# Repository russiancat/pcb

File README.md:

# PCB Auto-Router

A Python proof-of-concept for AI-assisted PCB routing. Import a KiCad board file, get it auto-routed in seconds.

**Status:** Active research / proof-of-concept. Not yet production-ready.

---

## What It Does

- Reads `.kicad_pcb` files (KiCad 7, 8, and 10 format)
- Auto-routes all nets using A* pathfinding on a 2-layer grid
- Supports copper pour (GND flood fill) on any layer
- Visualises the result as a two-panel image (top copper / bottom copper)
- Benchmarks against the existing routing in a file — measures completion %, wire length efficiency, via count, and DRC violations
- DRC checks: open nets, edge clearance, short circuits, pad clearance
- Manufacturer profiles with `merge()` for strictest-wins constraint checking

What it does **not** do (yet): schematic capture, auto-placement, Gerber export.

---

## Quick Start

```bash
# Install dependencies
python -m venv .venv
source .venv/bin/activate
pip install numpy matplotlib

# Route a KiCad board (outputs demo_result.png)
python kicad_demo.py path/to/your_board.kicad_pcb

# Run the benchmark across all demo boards
python benchmark.py
```

---

## Example Output

Two-panel view — top copper (F.Cu) and bottom copper (B.Cu) side by side.  
Legend below the board. GND copper pour shown as semi-transparent fill.

---

## Manufacturer Profiles

Profiles live in `router/profiles/*.toml`. Add a new manufacturer by adding one `.toml` file — no Python code needed.

| Profile | Trace / Clearance | Via drill | Via cost | Target |
|---------|------------------|-----------|----------|--------|
| `HOME_ETCH` | 1.0 mm | 0.8 mm | High | Toner transfer / UV home etching |
| `PCBWAY_2L` | 0.127 mm | 0.3 mm | Low | PCBWay 2-layer standard |
| `PCBWAY_4L` | 0.1 mm | 0.2 mm | Low | PCBWay 4-layer advanced |
| `JLCPCB_2L` | 0.127 mm | 0.3 mm | Low | JLCPCB 2-layer standard |
| `JLCPCB_4L` | 0.1 mm | 0.2 mm | Low | JLCPCB 4-layer advanced |
| `ZBOTIC_2L` | 0.15 mm | 0.3 mm | Low | ZBOTIC 2-layer |
| `ZBOTIC_4L` | 0.1 mm | 0.2 mm | Low | ZBOTIC 4-layer |

Change `PROFILE` at the top of `kicad_demo.py` to target a different fab.  
Use `ManufacturerProfile.merge(a, b)` to combine constraints (strictest-wins).

---

## Benchmark Results

Tested against KiCad demo boards using the same component placements, routing from scratch with a 0.5 mm benchmark grid (speed-optimised — use a manufacturer profile for real DRC).

| Board | Nets | Our routed | Our unrouted | KiCad routed | KiCad unrouted | Wire vs KiCad | Shorts | Quality |
|-------|------|-----------|-------------|-------------|---------------|---------------|--------|---------|
| multichannel_mixer | 80 | 79 (98.8%) | 1 | 79 (98.8%) | 1 | −7.0% shorter | ✓ | 75.9 |
| complex_hierarchy | 52 | 50 (96.2%) | 2 | 49 (94.2%) | 3 | −22.6% shorter | ✓ | 76.9 |
| ecc83-pp | 13 | 9 (69.2%) | 4 | 8 (61.5%) | 5 | −23.5% shorter | ✓ | 55.4 |
| ecc83-pp_v2 | 13 | 9 (69.2%) | 4 | 9 (69.2%) | 4 | −26.3% shorter | ✓ | 55.4 |
| interf_u | 173 | 102 (59.0%) | 71 | 110 (63.6%) | 63 | −8.2% shorter | ✓ | 47.2 |
| tinytapeout | 114 | 71 (62.3%) | 43 | 108 (94.7%) | 6 | −18.8% shorter | ✓ | 49.8 |
| pic_programmer | 111 | 34 (30.6%) | 77 | 0 (0%) | 111 | n/a | ✓ | — |
| CM5_MINIMA_3 | 220 | 47 (21.4%) | 173 | 96 (43.6%) | 124 | −14.6% shorter | ✓ | 17.1 |

**Zero short circuits on every board.** On nets we complete, our A* consistently produces shorter wire than the human/FreeRouting reference. Dense boards (CM5, tinytapeout) are limited by routing capacity — they need a finer grid (0.127 mm) or layer-aware global routing to improve completion.

---

## Architecture

```
.kicad_pcb
    → KiCadBoard parser (handles KiCad 7/8 + KiCad 10 format)
    → Grid (2D numpy array per copper layer)
        - EMPTY / OBSTACLE / net_id per cell
        - Edge keepout applied as obstacle border
        - Clearance enforced at query time (numpy slice)
    → GlobalRouter (tile-level congestion planning → cost_map)
    → Router
        - MST pad ordering (Prim's) — trunk-and-branch topology
        - A* pathfinding — 8-directional, via support
        - Rip-and-retry for failed nets
        - Copper pour (BFS flood-fill) for GND nets
    → DRC (open nets, edge clearance, short circuits, pad clearance)
    → Benchmark / quality scoring vs KiCad reference
```

---

## File Structure

```
router/
  board.py              Grid class — 2D numpy array per layer
  astar.py              A* pathfinding — 8-directional, via support
  router.py             Router — MST ordering, rip-and-retry, copper pour
  global_router.py      Tile-level congestion planning and cost map
  netlist.py            Pad / Net / Component frozen dataclasses
  design_rules.py       DesignRules dataclass (fields only — no presets)
  manufacturer_profile.py  ManufacturerProfile, load_all_profiles(), merge()
  drc.py                ViolationType, DRCViolation, run_drc(), check_profile_compatibility()
  quality.py            QualityReport, quality_report()
  kicad_parser.py       .kicad_pcb parser (KiCad 7/8 + 10)
  profiles/             Manufacturer specs as TOML files (one file per fab)
  __init__.py           POUR_NET_NAMES frozenset
visualize.py            Two-panel matplotlib visualisation (F.Cu / B.Cu)
kicad_demo.py           Route a single board from a .kicad_pcb file
benchmark.py            Benchmark all demo boards, compare vs KiCad reference
demo.py                 Synthetic 5-net demo board
crawl_training_data.py  Crawl GitHub for KiCad files → score → GNN training set
tests/                  pytest test suite
results/                Benchmark output images
kicad-demo/             KiCad demo boards (local copy)
data/                   Synthetic test boards
data/training/          GNN training data (downloaded by crawl_training_data.py)
CLAUDE.md               Project context for AI assistant sessions
```

---

## Roadmap

### Phase 1 — Router improvements (current)
- [x] A* routing with 2-layer via support
- [x] MST trunk-and-branch for multi-pin nets
- [x] Global routing (tile congestion map)
- [x] Copper pour (GND flood fill)
- [x] Edge keepout enforcement
- [x] Benchmark + quality scoring vs KiCad reference
- [x] DRC: open nets, edge clearance, short circuits, pad clearance
- [x] Manufacturer profiles (TOML, merge, check_profile_compatibility)
- [ ] Power net spine routing (dedicated trunk for VCC/vbias)
- [ ] Layer-aware global routing (assign nets to preferred layers)
- [ ] Negotiated congestion (PathFinder-style)

### Phase 2 — GNN-assisted routing
- [x] Collect training data — `crawl_training_data.py` crawls GitHub, scores boards, saves passing boards with companions to `data/training/`
- [ ] PathFinder baseline — negotiated congestion without ML, establishes improvement floor for GNN
- [ ] Graph extractor — `.kicad_pcb` → PyG `HeteroData` graph (components + nets + pads as typed nodes)
- [ ] GNN net ordering (Option B) — GAT encodes netlist, predicts net order + zone assignments, A* executes; validates that learned planning improves completion rate
- [ ] Routeability predictor — GNN surrogate estimates completion% from placement without running A*; prerequisite for auto-placement
- [ ] Iterative cooperative routing (Option D) — chunked GNN↔A* feedback loop with temporal attention over chunk history and rip-up decisions; see DECISIONS.md
- [ ] RL training loop — per-fab model, reward = hard constraints (shorts/fab violations/current capacity → R=0) × weighted product of soft objectives (completion², wire efficiency, via efficiency, DRC score, thermal score); per-chunk intermediate rewards with discount; see DECISIONS.md D4

### Phase 3 — Auto-placement
- [ ] GNN model: netlist graph → component positions
- [ ] Training data: KiCad boards with coordinates

### Phase 4 — Web product
- [ ] Web frontend (all routing in browser via WASM or API)
- [ ] Auth + S3 storage (no DB)
- [ ] Board size restriction for free tier
- [ ] KiCad export: write routed traces as `(segment ...)` / `(via ...)` nodes
- [ ] Gerber export (RS-274X native generator)

---

## Key Observations

- **Via cost must match the fab process.** Hand-drilled vias (home etch) are expensive; machine-drilled vias at JLCPCB are essentially free. Using a high via cost on dense boards causes routing failures because the router can't escape congestion without switching layers.
- **MST ordering beats sequential ordering** for multi-pin nets — power rails with many pads route 30–50% shorter by connecting the closest pair first and branching from there.
- **GND copper pour is essential** — routing GND as individual traces on a dense board fails. Flooding unused copper is both more reliable and more electrically sound.
- **On routable boards, our A* produces shorter wire than human routing.** The quality gap is about completion rate, not routing quality per se.

---

## License

To be decided. Intended as freeware for hobbyists.

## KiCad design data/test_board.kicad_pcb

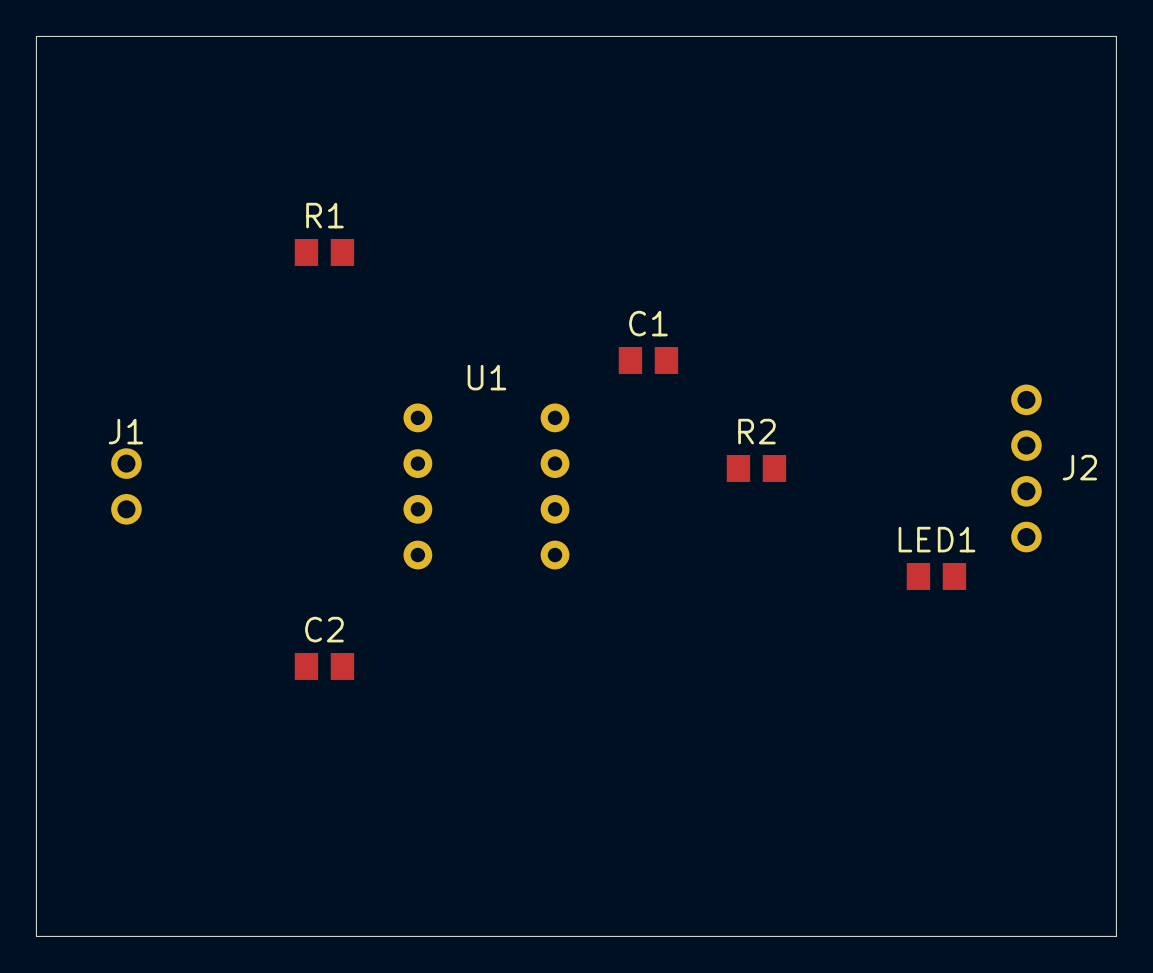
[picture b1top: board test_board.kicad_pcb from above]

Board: 0 copper layers, 60.0 x 50.0 mm, 8 parts (0 on the bottom side), 9 nets, no tracks yet.

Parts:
C1, C2: 100nF; C_0805
J1: PWR; PinHeader_2.54mm
J2: IO; PinHeader_2.54mm
LED1: RED; LED_0805
R1: 10k; R_0805
R2: 330R; R_0805
U1: ATtiny85; DIP-8_W7.62mm

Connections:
/LED_SIG: LED1.1, R2.2
/PB0: J2.1, U1.5
/PB1: J2.2, U1.6
/PB2: J2.3, U1.7
/PB3: R2.1, U1.2
/PB4: J2.4, U1.3
/RESET: R1.2, U1.1
GND: C1.2, C2.2, J1.2, LED1.2, U1.4
VCC: C1.1, C2.1, J1.1, R1.1, U1.8

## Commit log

2026-05-17 Initial commit: PCB auto-router proof of concept
    Two-layer A* router with zone-based global routing, MST trunk-and-branch,
    copper pour, and KiCad 7/8/10 parser. Benchmarks against KiCad reference
    routing on 8 demo boards — zero short circuits on all boards, wire
    consistently shorter than reference on completed nets.
    Architecture: GlobalRouter plans coarse tile corridors → congestion
    cost_map → A* detailed routing guided by soft congestion penalties →
2026-05-17 Add ZBOTIC_2L and ZBOTIC_4L design rule presets
    Specs from zbotic.in/pcb-technical-design-guidelines/:
    - 1-2 layer: 0.127mm trace/clearance, 0.15mm drill, 0.13mm annular
    - 4+ layer: 0.1mm trace/clearance, 0.15mm drill, 0.1mm annular
    Zbotic (Moxie Supply Pvt Ltd, Pune) is an Indian online fab with
    JLCPCB-class capability.
2026-05-17 Document export roadmap: kicad_pcb writer now, Gerber generator for web
2026-05-17 Add test suite and minor structural cleanup
    41 tests across 5 modules (board, astar, router, global_router,
    kicad_parser, design_rules) — all passing in 0.12s.
    Structural changes:
    - POUR_NET_NAMES moved to router/__init__.py (was duplicated in
    benchmark.py and kicad_demo.py)
    - Router gains verbose=True flag so tests run silently
2026-05-17 Refactor for SOLID / Elegant Objects compliance
    - router/drc.py: extract run_drc() with ViolationType enum + frozen DRCViolation
    - router/quality.py: extract quality_report() returning frozen QualityReport dataclass
    - router/board.py: add is_pad_cell() public method, removing _pad_cells leakage
    - router/router.py: verbose flag → logging; _mst_pad_order → Router staticmethod;
    route_all(nets_ordered=None) injection point for future GNN ordering
    - benchmark.py: import DRC/quality from new modules; use typed violation attrs
2026-05-17 CLAUDE.md: add Code Standards section (SOLID + Elegant Objects)
2026-05-17 Add ManufacturerProfile with PCBWay/JLCPCB/Zbotic presets and profile DRC
    - router/manufacturer_profile.py: ManufacturerProfile frozen dataclass with
    routing DesignRules + DRC-only fields (via diameter, PTH/NPTH drill, hole-to-hole,
    silkscreen). Presets: PCBWAY_2L/4L, JLCPCB_2L/4L, ZBOTIC_2L/4L.
    ManufacturerProfile.merge(*profiles) applies strictest-wins (max of mins, min of maxes).
    - router/drc.py: add TRACE_TOO_NARROW, VIA_DRILL_TOO_SMALL, VIA_DIAMETER_TOO_SMALL,
    ANNULAR_RING_TOO_NARROW violation types; add check_profile_compatibility(rules, profile)
2026-05-17 Move manufacturer specs to TOML config files; drop generic routing presets
    - router/profiles/*.toml: 7 TOML files (home_etch, pcbway_2l/4l, jlcpcb_2l/4l,
    zbotic_2l/4l) are now the single source of truth for all manufacturer specs.
    Adding a new manufacturer = adding a .toml file, no Python changes needed.
    - router/manufacturer_profile.py: rewritten as TOML loader; exposes named constants
    (HOME_ETCH, PCBWAY_2L, etc.) loaded at import time for convenient use.
    - router/design_rules.py: stripped to DesignRules dataclass only — no hardcoded presets.
2026-05-17 Freeze netlist dataclasses, typed RouteResult, updated docs
    - Pad, Net, Component are now frozen=True with pads: Tuple[Pad, ...]
    - kicad_parser, demo.py, and tests pass tuple(pads) at construction
    - benchmark.py: RouteResult frozen dataclass replaces raw dict return
    - visualize.py: print() replaced with logger.info()
    - README: new manufacturer profiles table, unrouted counts in benchmark
    table, added ecc83-pp_v2, corrected board names and percentages
2026-05-17 Add KiCad export (Phase 1): write routed traces back to .kicad_pcb
    router/kicad_writer.py: KiCadWriter class appends (segment ...) and
    (via ...) nodes to a copy of the source .kicad_pcb file. Segments
    carry proper layer names, trace width from DesignRules, net IDs, and
    UUID timestamps. Board-relative coordinates are translated back to
    KiCad space via board.origin_x/origin_y.
    kicad_demo.py: after routing, automatically writes <name>_routed.kicad_pcb
2026-05-17 Code review: fix type hints, PEP 8, vectorize DRC, make A* functions private
    - kicad_writer.py: one field per line in _Segment/_Via (PEP 8); type router param
    - quality.py: worse_nets fully typed as Tuple[Tuple[str, float, float, float], ...]
    - drc.py: nets: List[Net], router: Router; vectorize EDGE_CLEARANCE via numpy
    - astar.py: rename astar/astar_to_net to _astar/_astar_to_net (private)
    - router.py: update import and call sites
    - test_astar.py: import renamed symbols via alias so test names stay readable
2026-05-17 Add GitHub crawler for GNN training data collection
    crawl_training_data.py discovers KiCad repos via topic search (kicad,
    kicad-pcb, open-hardware, pcb-design) and GitHub code search
    (extension:kicad_pcb), downloads .kicad_pcb files, and scores each board
    against quality thresholds (≥5 nets, ≥75% routing completion, board
    10–500mm, ≤20% off-board components).
    State is persisted in data/training/visited.json (resumable) and
2026-05-17 crawler: interleave search and processing — stop searching at --max-repos
    Previously all search pages across all topics were fetched before any
    repo was processed. Now search is lazy: iter_repos_by_topic() and
    iter_repos_by_extension() yield one page at a time, and the main loop
    breaks as soon as the repo cap is hit. With --max-repos 20 the script
    makes ~1-2 search calls instead of 40+.
2026-05-17 crawler: only save boards that pass quality thresholds
    Score each file from a temp file in memory before writing anything to
    the training directory. Failing boards are discarded without touching
    disk; only passing .kicad_pcb + score.json files are kept.
2026-05-17 crawler: collect companion files and preserve repo directory structure
    For repos with at least one passing PCB, now also download:
    .kicad_sch / .sch — schematic (net labels, component types, hierarchy)
    .kicad_pro — project settings (net classes, per-class DRC rules)
    .kicad_dru — custom design rules (KiCad 7+ constraint scripts)
    Files are saved preserving the original repo path structure so hierarchical
    schematics and their sub-sheets stay correctly referenced relative to each
2026-05-17 crawler: per-PCB companion lookup in candidates.json, null for missing
    candidates.json now records schematic/project/design_rules paths per PCB
    using same-stem lookup in the same directory (standard KiCad layout).
    Missing companions are null, not omitted, so consumers know what's available.
    No name-collision issue — path structure is already preserved under repo_dir.
2026-05-17 crawler: fix KeyError 'file' — deduplication must use renamed key 'pcb_file'
2026-05-17 crawler: per-file 30s timeout + pre-write visited.json before processing
    Per-file timeout: _score_with_timeout() runs _score_from_bytes() in a
    single worker thread with a 30s deadline. A hung parser (malformed or
    enormous file) is abandoned and reported as a failing score — the crawler
    moves on to the next file without blocking. Downloads already had their
    own 60s timeout via requests.
    Pre-write: visited.json is written with the repo entry before process_repo
2026-05-17 crawler: fix timeout — shutdown(wait=False) so stuck thread is abandoned
    The previous implementation used `with ThreadPoolExecutor(...) as pool:`
    whose __exit__ calls shutdown(wait=True), blocking on the very thread we
    just timed out. Now we call shutdown(wait=False, cancel_futures=True)
    in a finally block so the main crawler moves on immediately.
2026-05-17 crawler: fix download hang + add visibility into which file is in flight
    - timeout=(10,30) tuple: 30s read timeout applies per chunk, not just
    first byte — stalled transfers are now abandoned after 30s inactivity
    - Skip tree entries >5MB (font/art PCBs with thousands of copper traces)
    - Print filename before download so stuck file is immediately visible
2026-05-17 crawler: fix _get read timeout + add diagnostic print after process_repo
    _get() used timeout=30 (connect only); now (10,30) tuple so read stalls
    also time out. Added "→ done" print immediately after process_repo returns
    to pinpoint whether hang is inside process_repo or in main() afterwards.
2026-05-17 crawler: show companion download progress + remove debug prints
    755 companion files downloading silently looked like a hang. Now each
    companion prints its index/total and name before downloading, so progress
    is visible. Removed the temporary DEBUG prints added during diagnosis.
2026-05-23 crawler: only download companions for passing PCB directories
2026-05-23 crawler: deduplicate PCBs by MD5 hash + one-time cleanup script
2026-05-23 crawler: fix 4-tuple unpack in passing_dirs after hash addition
2026-05-23 docs: add iterative cooperative routing (GNN↔A* feedback loop) as TODO
2026-05-23 docs: add DECISIONS.md architecture log + update CLAUDE.md ML TODOs
2026-05-23 docs: update README Phase 2 roadmap with full reward function and architecture detail
